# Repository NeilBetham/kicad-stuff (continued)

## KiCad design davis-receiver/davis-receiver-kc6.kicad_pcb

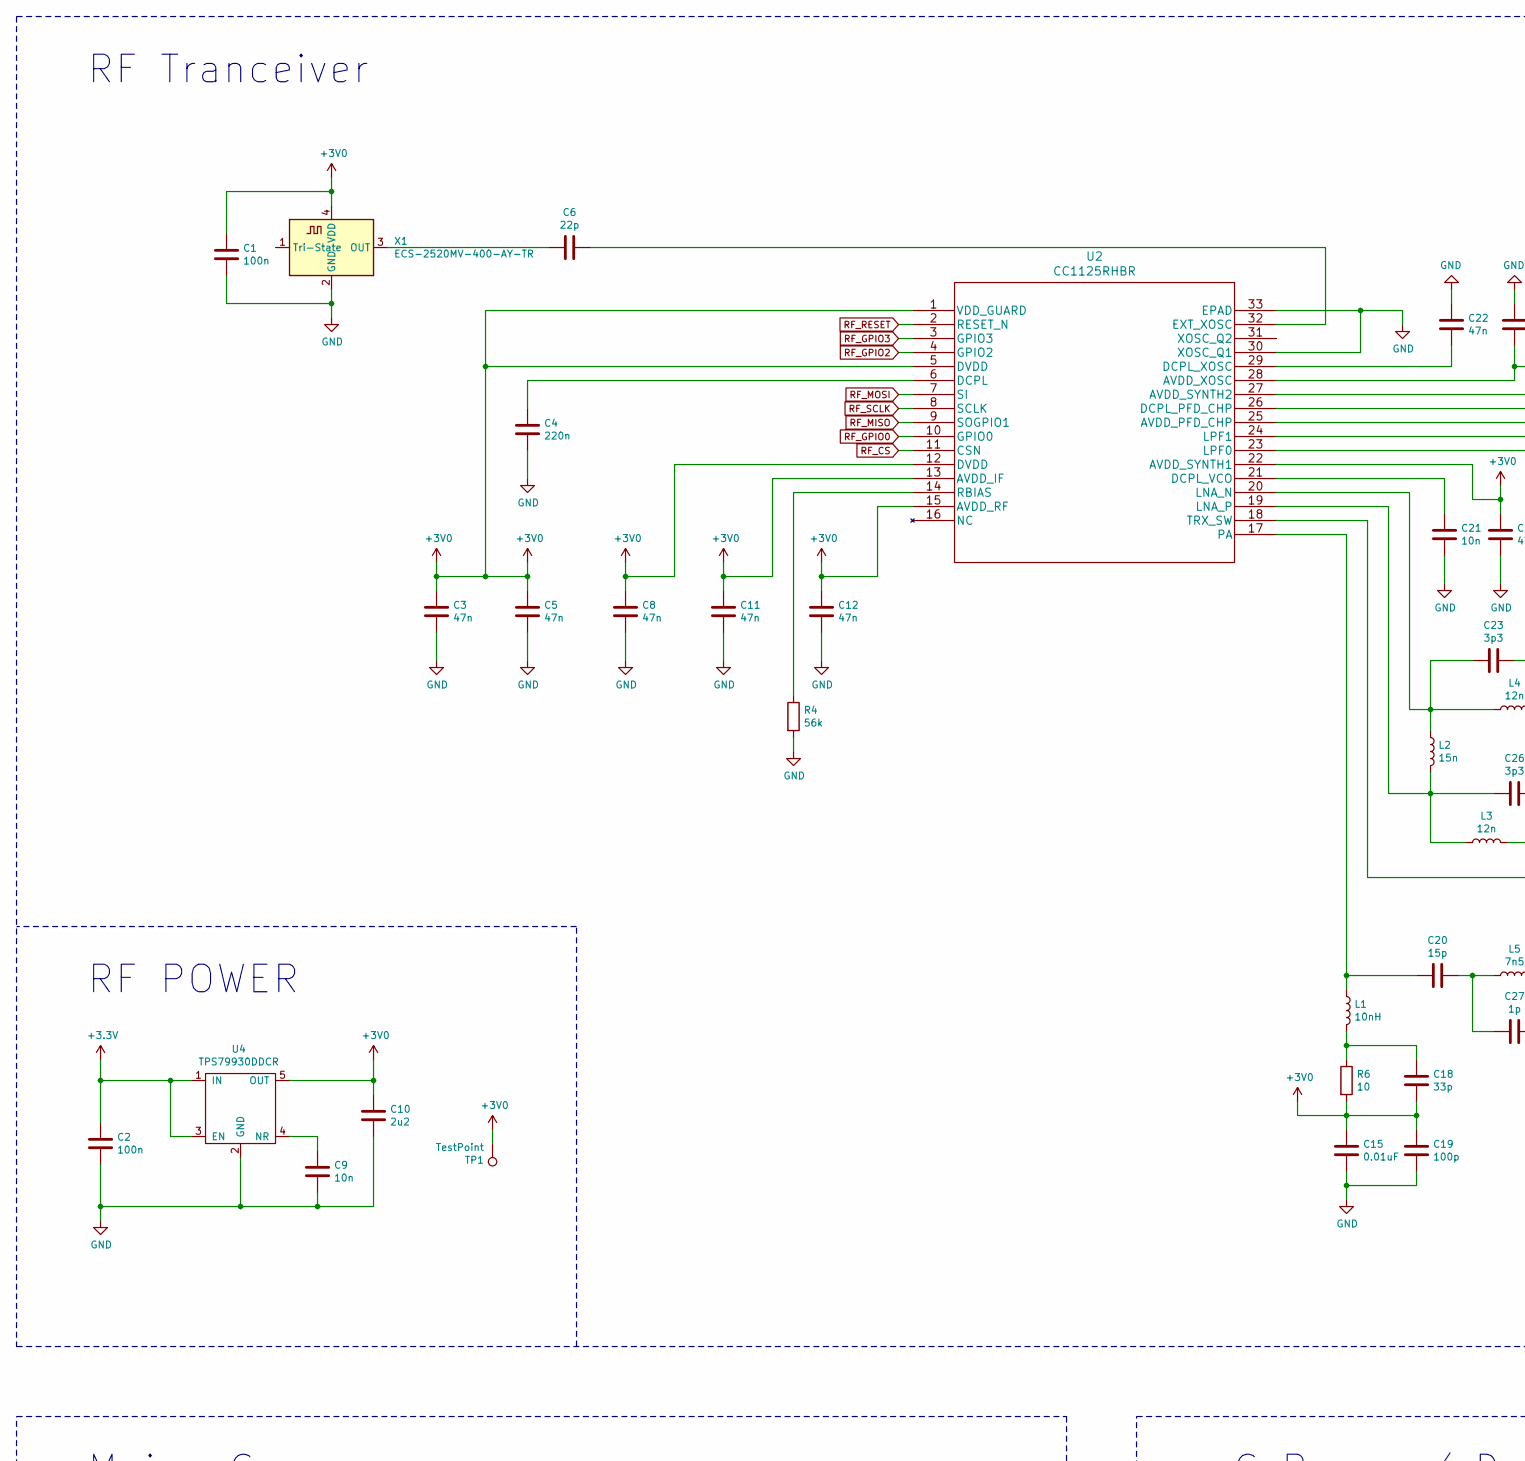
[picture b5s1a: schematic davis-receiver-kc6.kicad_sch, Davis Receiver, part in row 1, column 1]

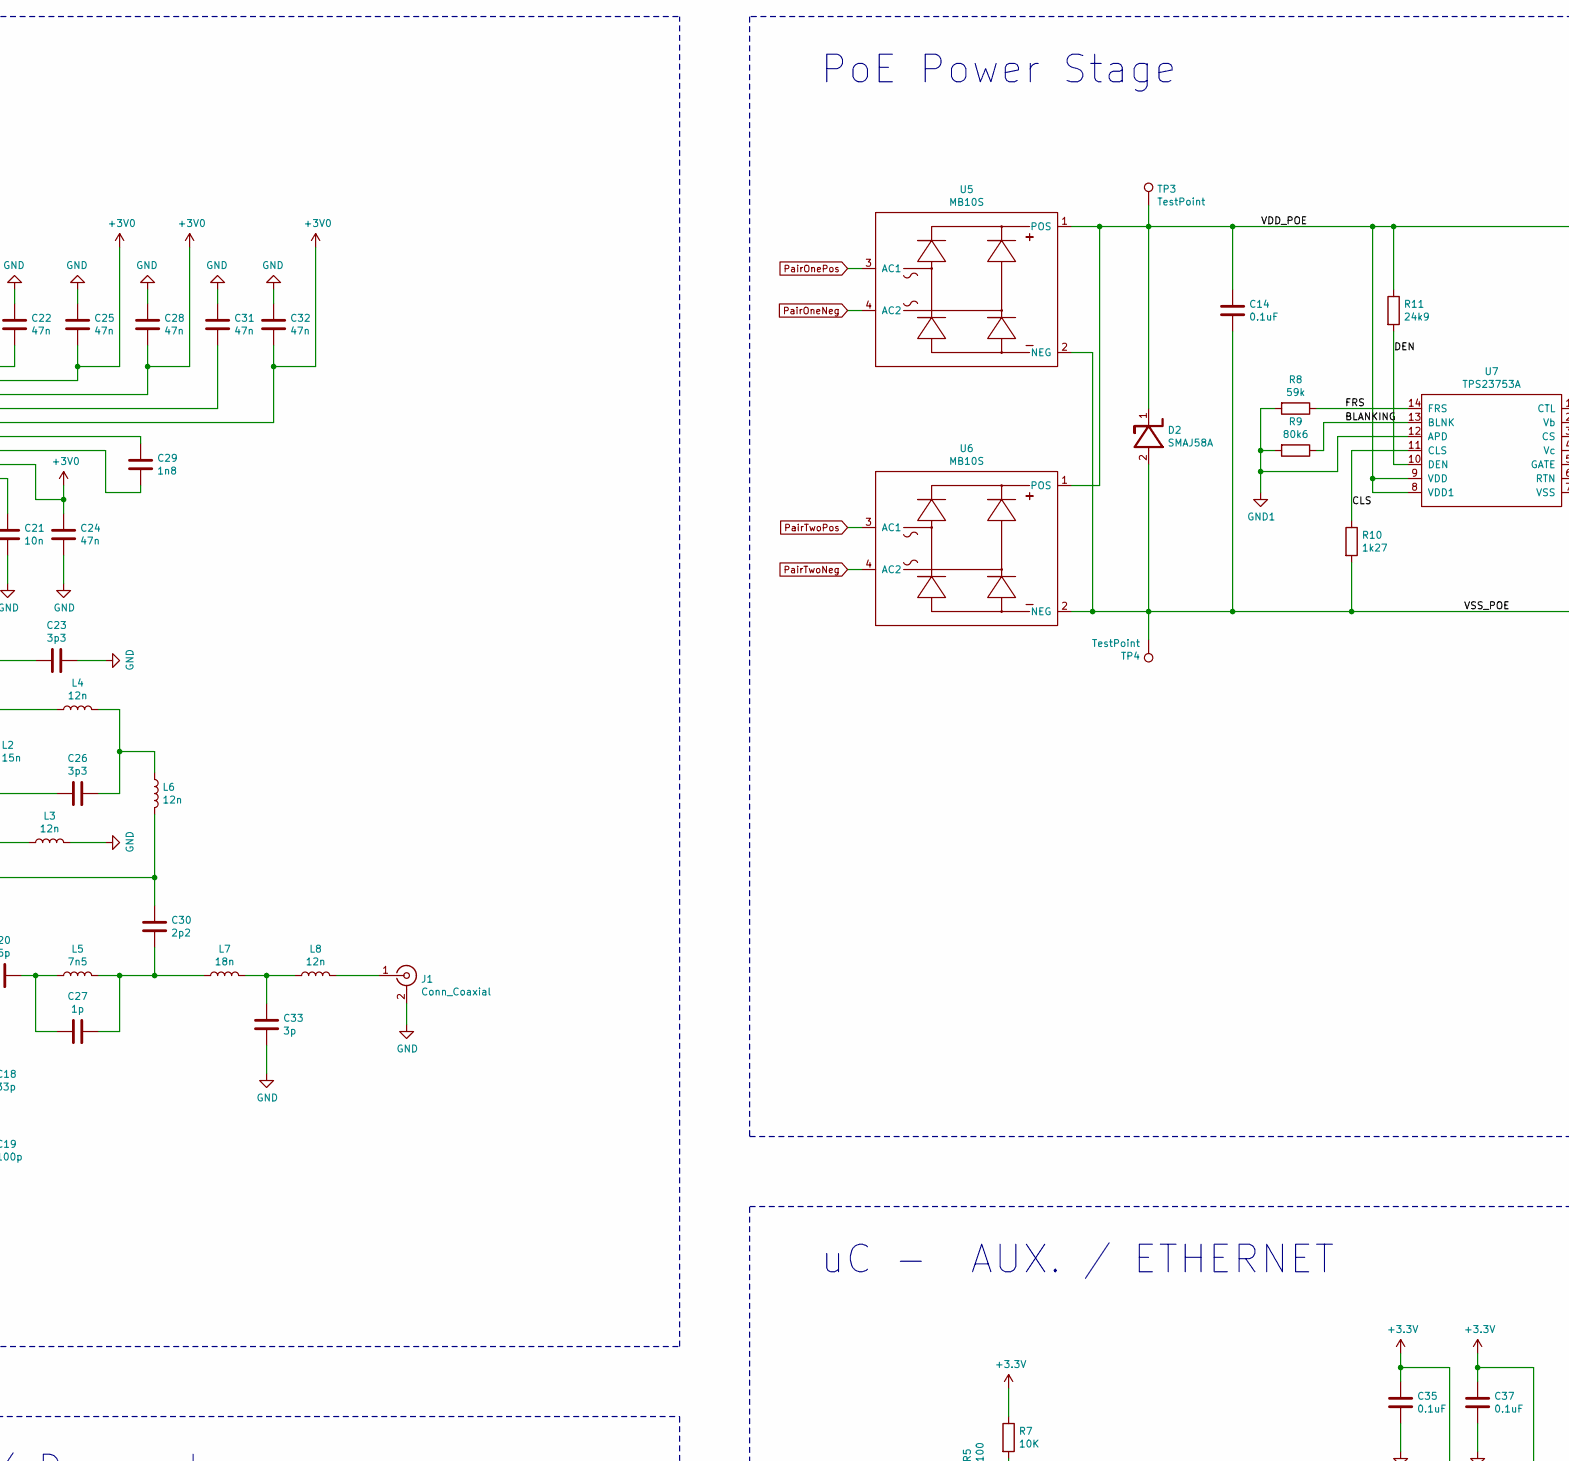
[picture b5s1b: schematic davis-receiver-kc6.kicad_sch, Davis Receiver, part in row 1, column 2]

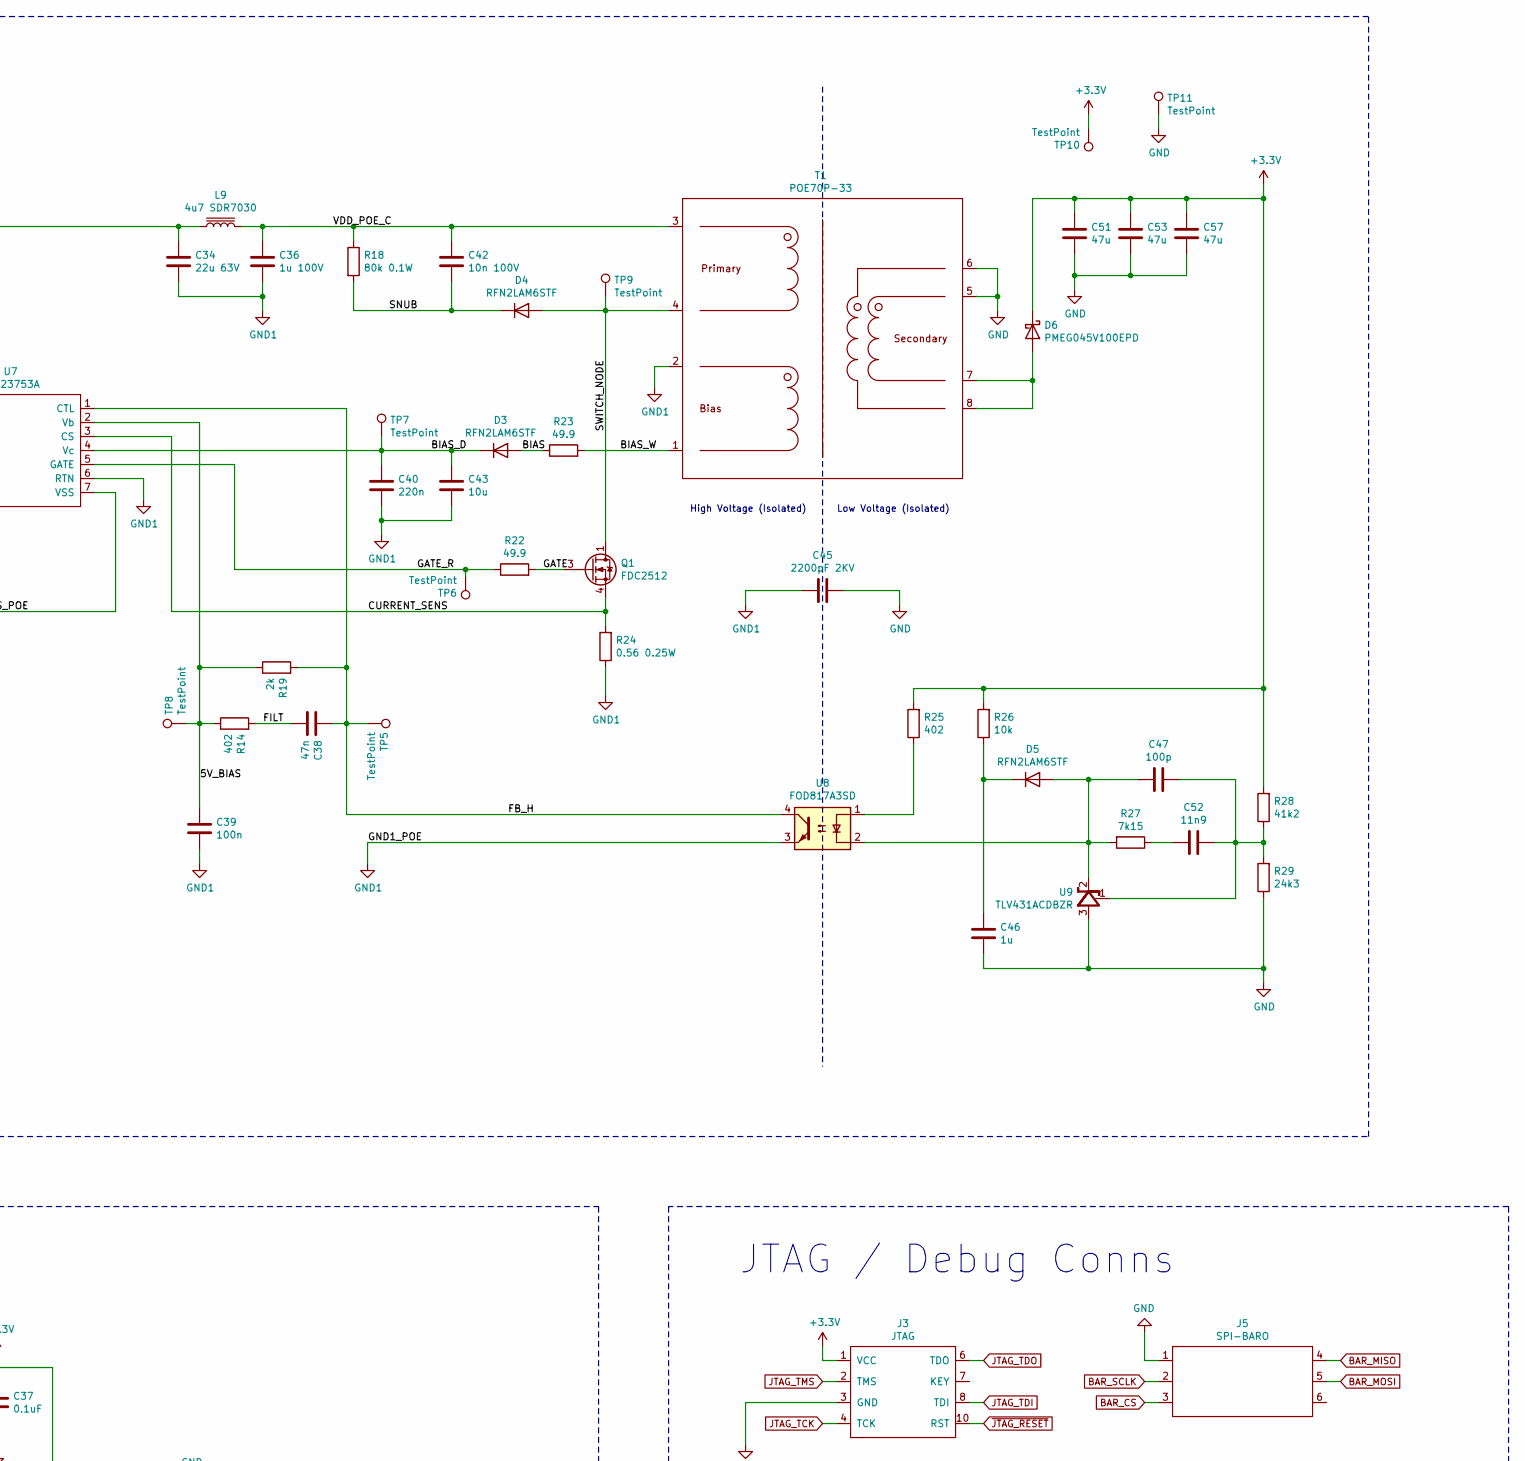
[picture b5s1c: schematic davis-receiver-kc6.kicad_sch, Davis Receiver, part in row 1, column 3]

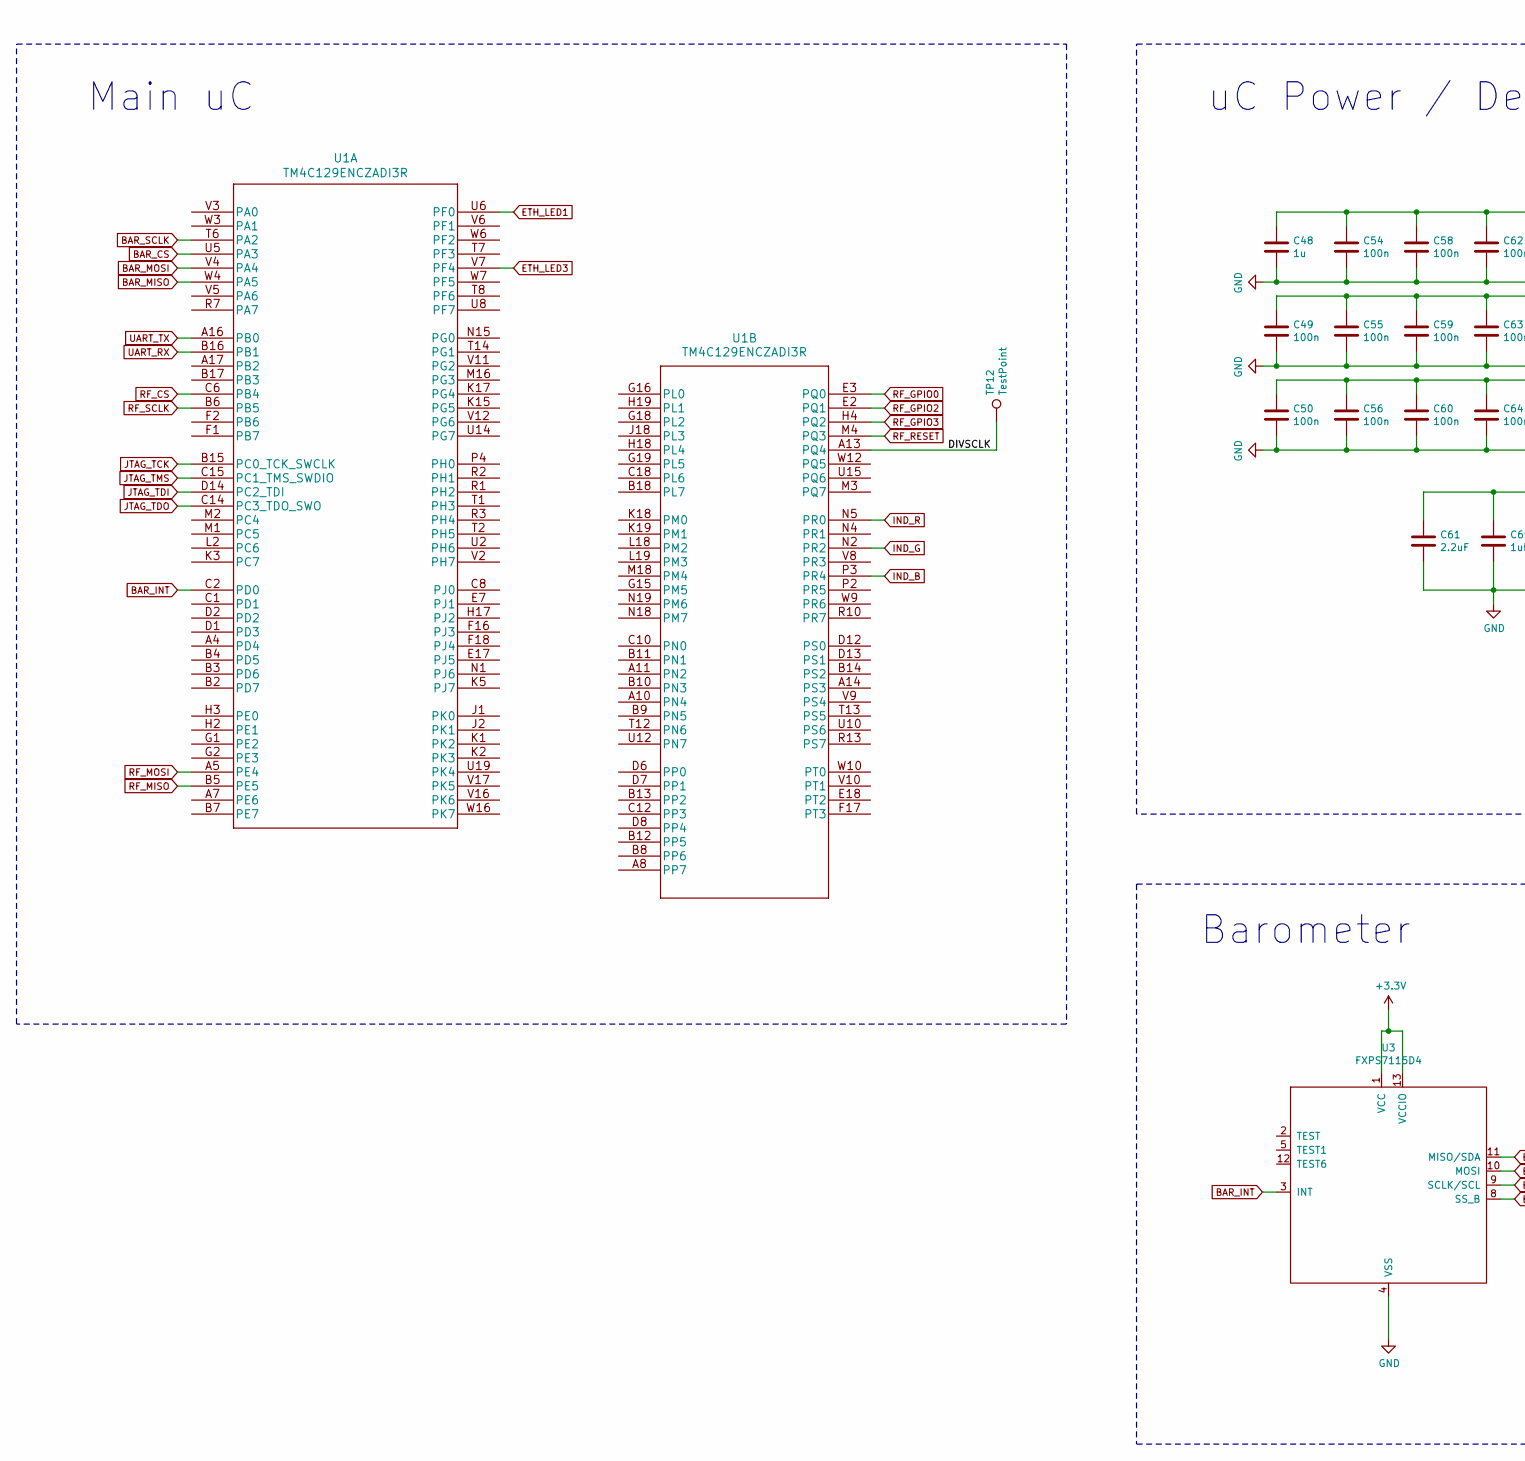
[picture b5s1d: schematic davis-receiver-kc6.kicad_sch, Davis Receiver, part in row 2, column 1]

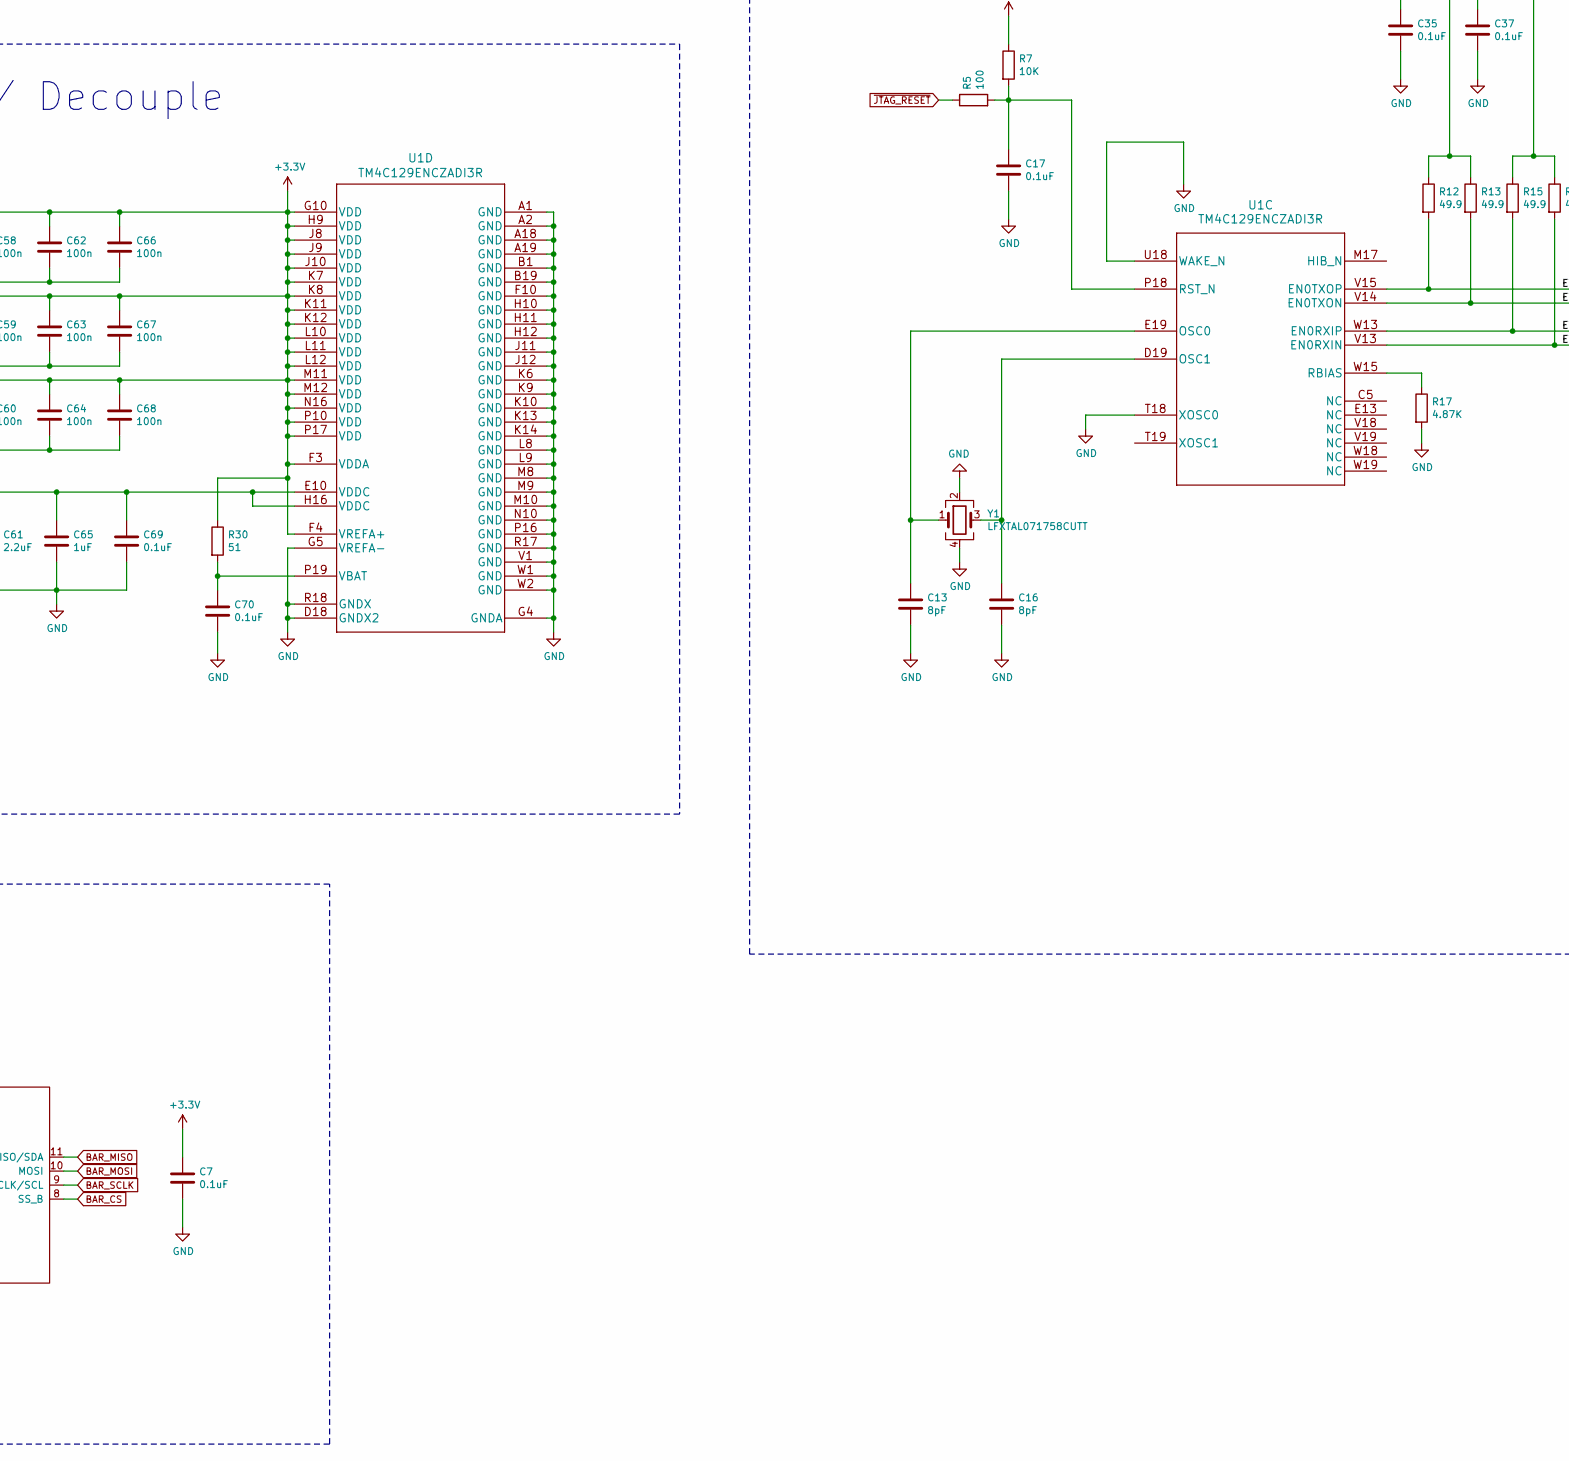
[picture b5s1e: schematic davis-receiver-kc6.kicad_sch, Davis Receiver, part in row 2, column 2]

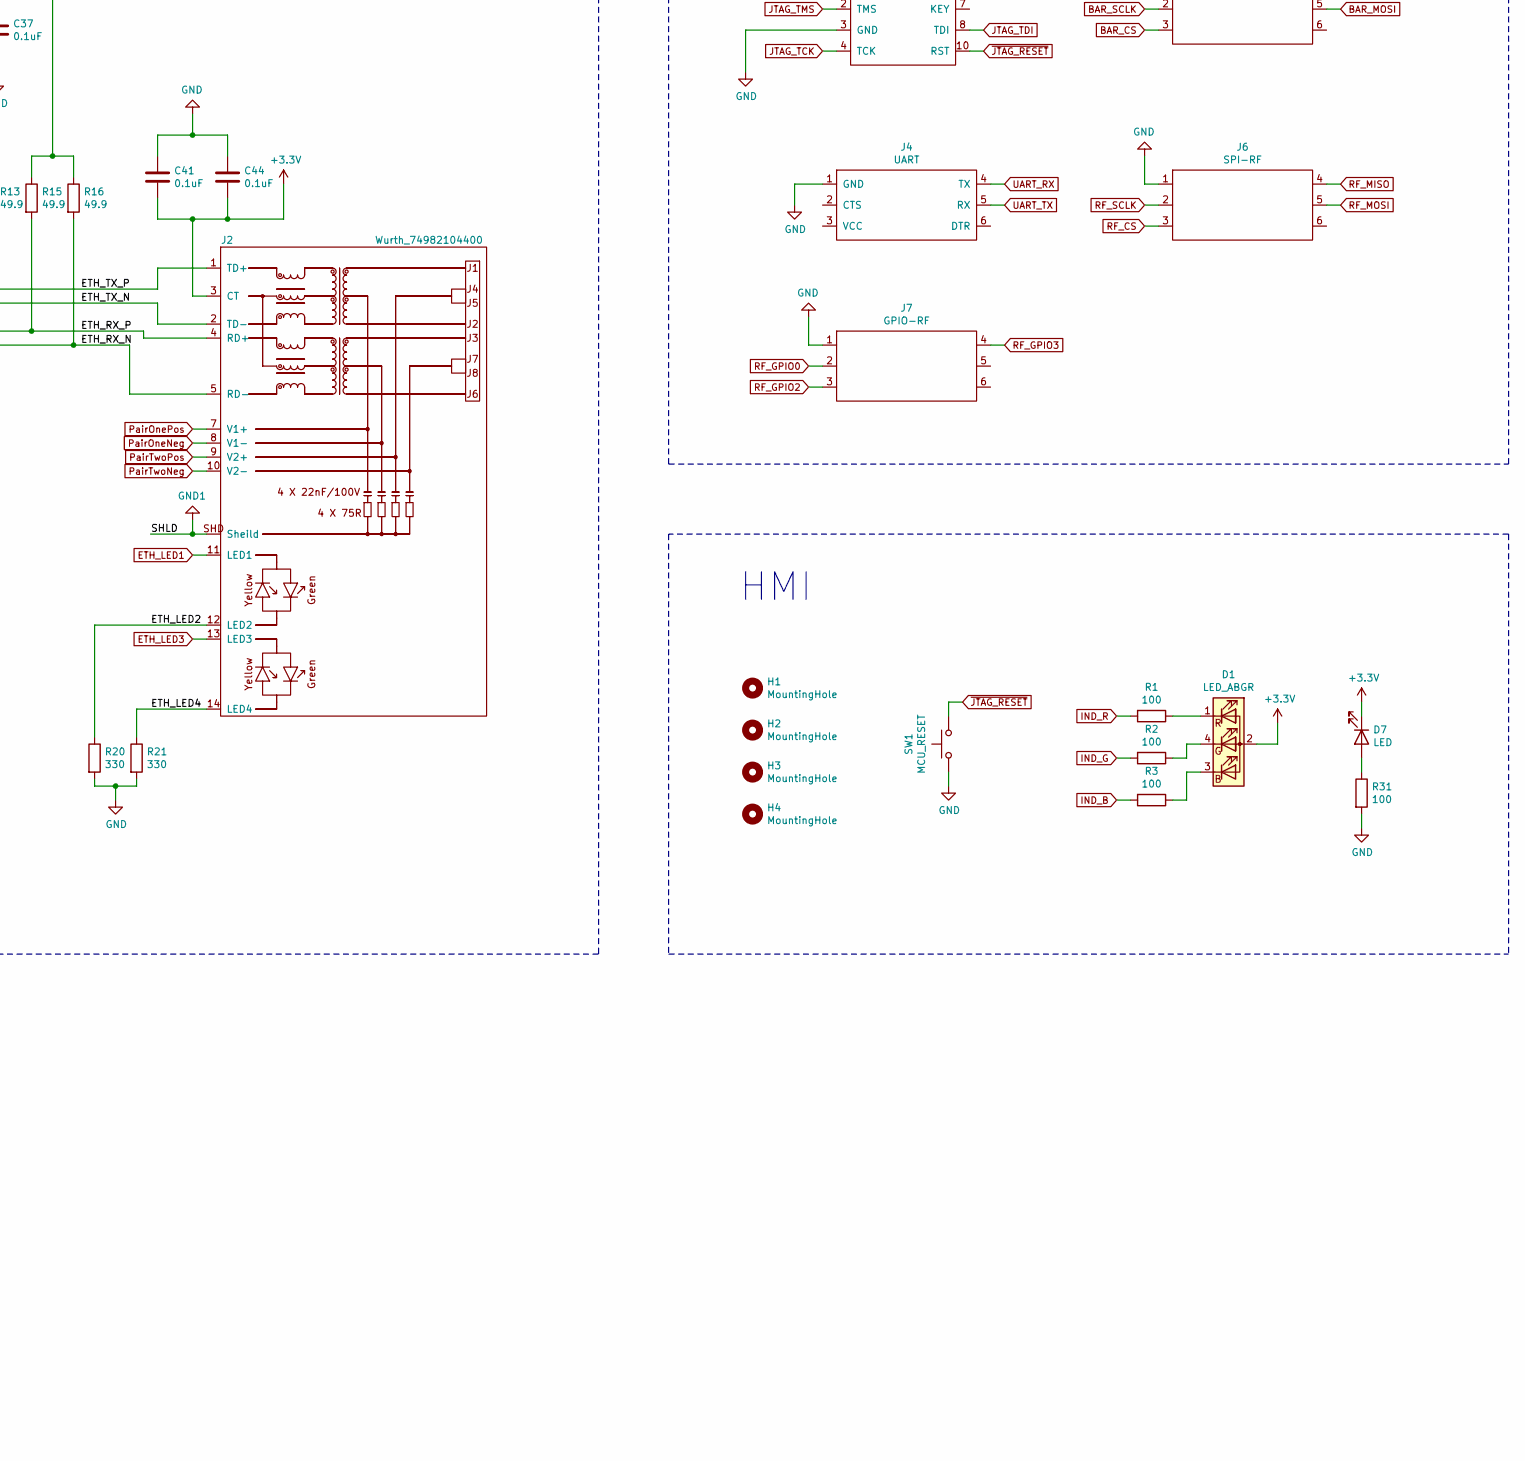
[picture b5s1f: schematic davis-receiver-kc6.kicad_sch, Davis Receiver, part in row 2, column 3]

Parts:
C1, C2, C39, C49, C50, C54, C55, C56, C58, C59, C60, C62, C63, C64, C66, C67, C68: 100n; C_0805_2012Metric
C3, C5, C8, C11, C12, C22, C24, C25, C28, C31, C32, C38: 47n; C_0805_2012Metric
C4, C40: 220n; C_0805_2012Metric
C6: 22p; C_0805_2012Metric
C7, C14, C17, C35, C37, C41, C44, C69, C70: 0.1uF; C_0805_2012Metric
C9, C21: 10n; C_0805_2012Metric
C10: 2u2; C_0805_2012Metric
C13, C16: 8pF; C_0805_2012Metric
C15: 0.01uF; C_0805_2012Metric
C18: 33p; C_0805_2012Metric
C19, C47: 100p; C_0805_2012Metric
C20: 15p; C_0805_2012Metric
C23, C26: 3p3; C_0805_2012Metric
C27: 1p; C_0805_2012Metric
C29: 1n8; C_0805_2012Metric
C30: 2p2; C_0805_2012Metric
C33: 3p; C_0805_2012Metric
C34: 22u 63V; C_2220_5650Metric
C36: 1u 100V; C_0805_2012Metric
C42: 10n 100V; C_0805_2012Metric
C43: 10u; C_0805_2012Metric
C45: 2200pF 2KV; C_1206_3216Metric
C46, C48: 1u; C_0805_2012Metric
C51, C53, C57: 47u; C_0805_2012Metric
C52: 11n9; C_0805_2012Metric
C61: 2.2uF; C_0805_2012Metric
C65: 1uF; C_0805_2012Metric
D1: LED_ABGR; LED_Cree-PLCC4_3.2x2.8mm_CCW
D2: SMAJ58A
D3, D4, D5: RFN2LAM6STF
D6: PMEG045V100EPD; CFP15
D7: LED; LED_1206_3216Metric
H1, H2, H3, H4: MountingHole; MountingHole_4.3mm_M4_Pad_Via
J1: Conn_Coaxial; CONREVSMA003.062-G
J2: Wurth_74982104400
J3: JTAG; TC2050-IDC-FP
J4: UART; TC2030-IDC-FP
J5: SPI-BARO; TC2030-IDC-FP
J6: SPI-RF; TC2030-IDC-FP
J7: GPIO-RF; TC2030-IDC-FP
L1: 10nH; L_0805_2012Metric
L2: 15n; L_0805_2012Metric
L3, L4, L6, L8: 12n; L_0805_2012Metric
L5: 7n5; L_0805_2012Metric
L7: 18n; L_0805_2012Metric
L9: 4u7 SDR7030; SDR7030
Q1: FDC2512; SuperSOT-6
R1, R2, R3, R5, R31: 100; R_0805_2012Metric
R4: 56k; R_0805_2012Metric
R6: 10; R_0805_2012Metric
R7: 10K; R_0805_2012Metric
R8: 59k; R_0805_2012Metric
R9: 80k6; R_0805_2012Metric
R10: 1k27; R_0805_2012Metric
R11: 24k9; R_0805_2012Metric
R12, R13, R15, R16, R22, R23: 49.9; R_0805_2012Metric
R14, R25: 402; R_0805_2012Metric
R17: 4.87K; R_0805_2012Metric
R18: 80k 0.1W; R_0805_2012Metric
R19: 2k; R_0805_2012Metric
R20, R21: 330; R_0805_2012Metric
R24: 0.56 0.25W; R_0805_2012Metric
R26: 10k; R_0805_2012Metric
R27: 7k15; R_0805_2012Metric
R28: 41k2; R_0805_2012Metric
R29: 24k3; R_0805_2012Metric
R30: 51; R_0805_2012Metric
SW1: MCU_RESET; PTS636
T1: POE70P-33; POE70P
TP1, TP3, TP4, TP5, TP6, TP7, TP8, TP9, TP10, TP11: TestPoint; TestPoint_Pad_D2.0mm
TP12: TestPoint; TestPoint_Pad_D1.0mm
U1: TM4C129ENCZADI3R
U2: CC1125RHBR
U3: FXPS7115D4; HQFN-16-4x4-1.98x0.8
U4: TPS79930DDCR; SOT-23-Thin-5
U5, U6: MB10S; SOIC-4W
U7: TPS23753A; TSSOP-14_4.4x5mm_P0.65mm
U8: FOD817A3SD; SMD-4
U9: TLV431ACDBZR; SOT-23
X1: ECS-2520MV-400-AY-TR; Oscillator_SMD_ECS_2520MV-xxx-xx-4Pin_2.5x2.0mm
Y1: LFXTAL071758CUTT

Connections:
+3V0: C1.1, C3.1, C5.1, C8.1, C10.1, C11.1, C12.1, C15.1, C18.2, C19.1, C24.1, C25.2, C28.2, C32.2, R6.2, TP1.1, U2.1 (VDD_GUARD), U2.5 (DVDD), U2.12 (DVDD), U2.13 (AVDD_IF), U2.15 (AVDD_RF), U2.22 (AVDD_SYNTH1), U2.25 (AVDD_PFD_CHP), U2.27 (AVDD_SYNTH2), U2.28 (AVDD_XOSC), U4.5 (OUT), X1.4 (VDD)
+3V3: C2.1, C7.1, C35.1, C37.1, C41.2, C44.2, C48.1, C49.1, C50.1, C51.1, C53.1, C54.1, C55.1, C56.1, C57.1, C58.1, C59.1, C60.1, C62.1, C63.1, C64.1, C66.1, C67.1, C68.1, D1.2 (A), D6.1 (K), D7.1 (K), J2.3 (CT), J3.1 (VCC), R7.1, R12.1, R13.1, R15.1, R16.1, R25.2, R26.2, R28.2, R30.1, TP10.1, U1.F3 (VDDA), U1.F4 (VREFA+), U1.G10 (VDD), U1.H9 (VDD), U1.J8 (VDD), U1.J9 (VDD), U1.J10 (VDD), U1.K7 (VDD), U1.K8 (VDD), U1.K11 (VDD), U1.K12 (VDD), U1.L10 (VDD), U1.L11 (VDD), U1.L12 (VDD), U1.M11 (VDD), U1.M12 (VDD), U1.N16 (VDD), U1.P10 (VDD), U1.P17 (VDD), U3.1 (VCC), U3.13 (VCCIO), U3.16 (VCC), U4.1 (IN), U4.3 (EN)
/5V_BIAS: C39.1, R14.1, R19.1, TP8.1, U7.2 (Vb)
/BIAS: D3.2 (A), R23.1
/BIAS_D: C40.1, C43.1, D3.1 (K), TP7.1, U7.4 (Vc)
/BIAS_W: R23.2, T1.1
/BLANKING: R9.1, U7.13 (BLNK)
/CLS: R10.1, U7.11 (CLS)
/CURRENT_SENS: Q1.4 (S), R24.2, U7.3 (CS)
/DEN: R11.2, U7.10 (DEN)
/DIVSCLK: TP12.1, U1.A13 (PQ4)
/ETH_LED2: J2.12 (LED2), R20.1
/ETH_LED4: J2.14 (LED4), R21.1
/ETH_RX_N: J2.5 (RD-), R16.2, U1.V13 (EN0RXIN)
/ETH_RX_P: J2.4 (RD+), R15.2, U1.W13 (EN0RXIP)
/ETH_TX_N: J2.2 (TD-), R13.2, U1.V14 (EN0TXON)
/ETH_TX_P: J2.1 (TD+), R12.2, U1.V15 (EN0TXOP)
/FB_H: C38.1, R19.2, TP5.1, U7.1 (CTL), U8.4
/FILT: C38.2, R14.2
/FRS: R8.1, U7.14 (FRS)
/GATE: Q1.3 (G), R22.2
/GATE_R: R22.1, TP6.1, U7.5 (GATE)
/SNUB: C42.2, D4.1 (K), R18.2
/SWITCH_NODE: D4.2 (A), Q1.1 (D), Q1.2 (D), Q1.5 (D), Q1.6 (D), T1.4, TP9.1
/VDD_POE: C14.1, C34.1, D2.1, L9.1, R11.1, TP3.1, U5.1 (POS), U6.1 (POS), U7.8 (VDD1), U7.9 (VDD)
/VDD_POE_C: C36.1, C42.1, L9.2, R18.1, T1.3
/VSS_POE: C14.2, D2.2, R10.2, TP4.1, U5.2 (NEG), U6.2 (NEG), U7.7 (VSS)
BAR_CS: J5.3, U1.U5 (PA3), U3.8 (SS_B)
BAR_INT: U1.C2 (PD0), U3.3 (INT)
BAR_MISO: J5.4, U1.W4 (PA5), U3.11 (MISO/SDA)
BAR_MOSI: J5.5, U1.V4 (PA4), U3.10 (MOSI)
BAR_SCLK: J5.2, U1.T6 (PA2), U3.9 (SCLK/SCL)
ETH_LED1: J2.11 (LED1), U1.U6 (PF0)
ETH_LED3: J2.13 (LED3), U1.V7 (PF4)
GND: C1.2, C2.2, C3.2, C4.2, C5.2, C7.2, C8.2, C9.2, C10.2, C11.2, C12.2, C13.2, C15.2, C16.2, C17.2, C19.2, C21.2, C22.1, C23.2, C24.2, C25.1, C28.1, C31.1, C32.1, C33.2, C35.2, C37.2, C41.1, C44.1, C45.1, C46.1, C48.2, C49.2, C50.2, C51.2, C53.2, C54.2, C55.2, C56.2, C57.2, C58.2, C59.2, C60.2, C61.2, C62.2, C63.2, C64.2, C65.2, C66.2, C67.2, C68.2, C69.2, C70.2, J1.2 (Ext), J3.3 (GND), J4.1 (GND), J5.1, J6.1, J7.1, L3.2, R4.2, R17.2, R20.2, R21.2, R29.1, R31.2, SW1.1, T1.5, T1.6, TP11.1, U1.A1 (GND), U1.A2 (GND), U1.A18 (GND), U1.A19 (GND), U1.B1 (GND), U1.B19 (GND), U1.D18 (GNDX2), U1.F10 (GND), U1.G4 (GNDA), U1.G5 (VREFA-), U1.H10 (GND), U1.H11 (GND), U1.H12 (GND), U1.J11 (GND), U1.J12 (GND), U1.K6 (GND), U1.K9 (GND), U1.K10 (GND), U1.K13 (GND), U1.K14 (GND), U1.L8 (GND), U1.L9 (GND), U1.M8 (GND), U1.M9 (GND), U1.M10 (GND), U1.N10 (GND), U1.P16 (GND), U1.R17 (GND), U1.R18 (GNDX), U1.T18 (XOSC0), U1.U18 (WAKE_N), U1.V1 (GND), U1.W1 (GND), U1.W2 (GND), U2.30 (XOSC_Q1), U2.33 (EPAD), U3.4 (VSS), U3.15 (VSS), U3.17 (VSS), U4.2 (GND), U9.3, X1.2 (GND), Y1.2, Y1.4
GND1: C34.2, C36.2, C39.2, C40.2, C43.2, C45.2, J2.SHD (Sheild), R8.2, R9.2, R24.1, T1.2, U7.6 (RTN), U7.12 (APD), U8.3
IND_B: R3.2, U1.P3 (PR4)
IND_G: R2.2, U1.N2 (PR2)
IND_R: R1.2, U1.N5 (PR0)
JTAG_TCK: J3.4 (TCK), U1.B15 (PC0_TCK_SWCLK)
JTAG_TDI: J3.8 (TDI), U1.D14 (PC2_TDI)
JTAG_TDO: J3.6 (TDO), U1.C14 (PC3_TDO_SWO)
JTAG_TMS: J3.2 (TMS), U1.C15 (PC1_TMS_SWDIO)
unnamed: C4.1, U2.6 (DCPL)
unnamed: C6.1, X1.3 (OUT)
unnamed: C6.2, U2.32 (EXT_XOSC)
unnamed: C9.1, U4.4 (NR)
unnamed: C13.1, U1.E19 (OSC0), Y1.1
unnamed: C16.1, U1.D19 (OSC1), Y1.3
unnamed: C17.1, R5.2, R7.2, U1.P18 (RST_N)
unnamed: C18.1, L1.2, R6.1
unnamed: C20.1, L1.1, U2.17 (PA)
unnamed: C20.2, C27.1, L5.1
unnamed: C21.1, U2.21 (DCPL_VCO)
unnamed: C22.2, U2.29 (DCPL_XOSC)
unnamed: C23.1, L2.1, L4.1, U2.20 (LNA_N)
unnamed: C26.1, L2.2, L3.1, U2.19 (LNA_P)
unnamed: C26.2, L4.2, L6.1
unnamed: C27.2, C30.2, L5.2, L7.1
unnamed: C29.1, U2.24 (LPF1)
unnamed: C29.2, U2.23 (LPF0)
unnamed: C30.1, L6.2, U2.18 (TRX_SW)
unnamed: C31.2, U2.26 (DCPL_PFD_CHP)
unnamed: C33.1, L7.2, L8.1
unnamed: C46.2, D5.1 (K), R26.1
unnamed: C47.1, D5.2 (A), R27.2, U8.2, U9.2
unnamed: C47.2, C52.2, R28.1, R29.2, U9.1
unnamed: C52.1, R27.1
unnamed: C61.1, C65.1, C69.1, U1.E10 (VDDC), U1.H16 (VDDC)
unnamed: C70.1, R30.2, U1.P19 (VBAT)
unnamed: D1.1 (RK), R1.1
unnamed: D1.3 (BK), R3.1
unnamed: D1.4 (GK), R2.1
unnamed: D6.2 (A), T1.7, T1.8
unnamed: D7.2 (A), R31.1
unnamed: J1.1 (In), L8.2
unnamed: R4.1, U2.14 (RBIAS)
unnamed: R17.1, U1.W15 (RBIAS)
unnamed: R25.1, U8.1
PairOneNeg: J2.8 (V1-), U5.4 (AC2)
PairOnePos: J2.7 (V1+), U5.3 (AC1)
PairTwoNeg: J2.10 (V2-), U6.4 (AC2)
PairTwoPos: J2.9 (V2+), U6.3 (AC1)
RF_CS: J6.3, U1.C6 (PB4), U2.11 (CSN)
RF_GPIO0: J7.2, U1.E3 (PQ0), U2.10 (GPIO0)
RF_GPIO2: J7.3, U1.E2 (PQ1), U2.4 (GPIO2)
RF_GPIO3: J7.4, U1.H4 (PQ2), U2.3 (GPIO3)
RF_MISO: J6.4, U1.B5 (PE5), U2.9 (SOGPIO1)
RF_MOSI: J6.5, U1.A5 (PE4), U2.7 (SI)
RF_RESET: U1.M4 (PQ3), U2.2 (RESET_N)
RF_SCLK: J6.2, U1.B6 (PB5), U2.8 (SCLK)
UART_RX: J4.4 (TX), U1.B16 (PB1)
UART_TX: J4.5 (RX), U1.A16 (PB0)
~JTAG_RESET: J3.10 (RST), R5.1, SW1.2

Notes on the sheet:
Low Voltage (Isolated)
PoE Power Stage
JTAG / Debug Conns
High Voltage (Isolated)
Main uC
HMI
RF POWER
uC Power / Decouple
Barometer
uC - AUX. / ETHERNET
RF Tranceiver

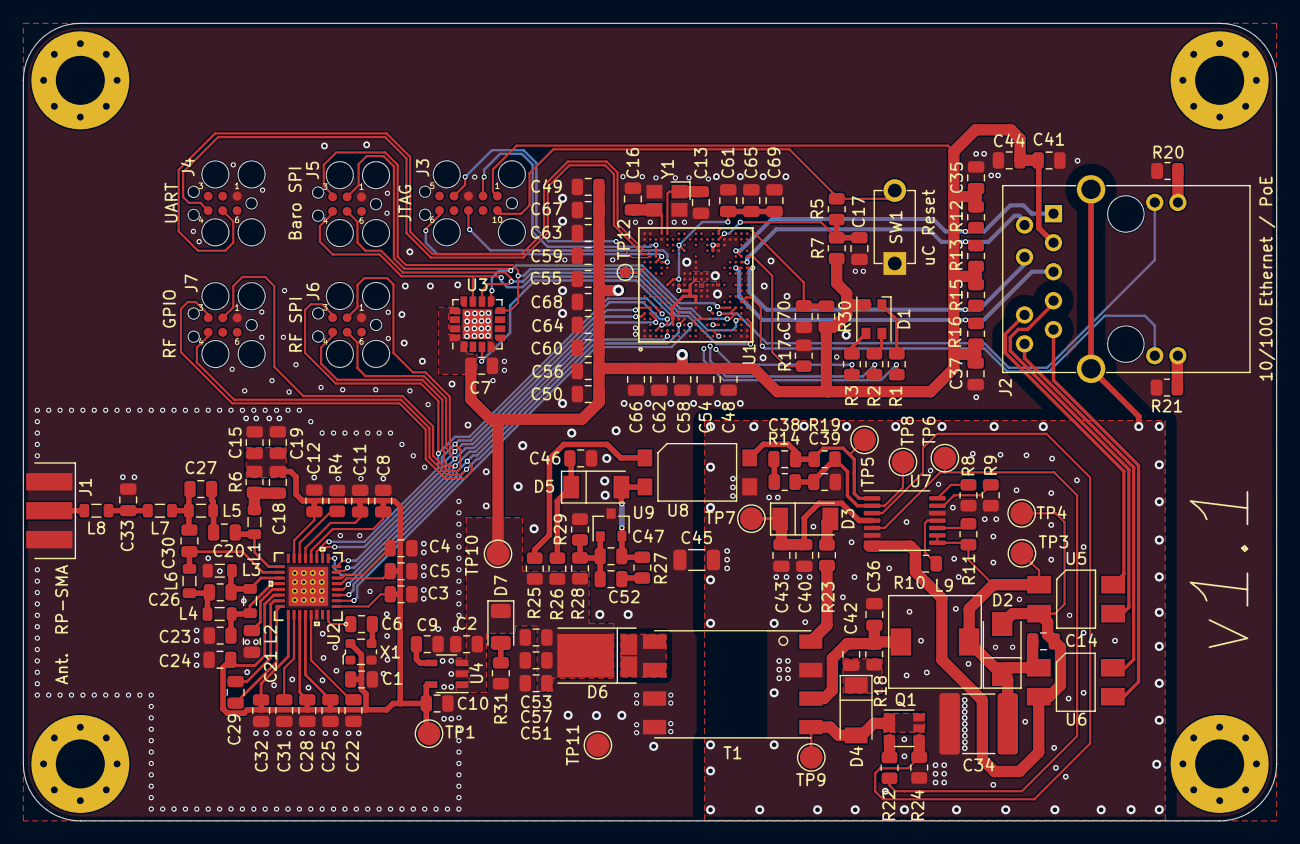
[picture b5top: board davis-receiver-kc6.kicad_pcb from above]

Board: 4 copper layers, 110.0 x 70.0 mm, 153 parts (0 on the bottom side), 94 nets.
